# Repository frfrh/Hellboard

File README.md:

# Hellboard

This is a Macro board based on RP2040-zero and Micropython, meant for ordering Stratagems for Helldivers 2 by registering as a HID-Keyboard.

## Hellboard Companion

The Hellboard Companion is a Windows app that puts your stratagems on the Hellboard automatically. It watches the Helldivers 2 loadout screen, recognizes the four stratagems you pick and the optional mission stratagems, and sends them to the board as soon as you press *Ready*. You don't have to configure any buttons by hand. The app also configures the board and installs firmware updates, so you need nothing else to use the Hellboard.

Download it from the [releases](https://github.com/frfrh/Hellboard/releases). More details: [`Software/README.md`](Software/README.md).

### Three stratagems need a one-time setup

The game draws three stratagems differently from the icon set the Companion compares with, so they are reported as *not recognized* at first:

- **EAT-17 Expendable Anti-Tank** and **EAT-411 Leveller** – the game adds a small badge to the icon.
- **TD-220 Bastion MK XVI** – the icon set shows the Maelstrom for it. Until you set it up, a Maelstrom may also be taken for the Bastion.

Teach the Companion how they look in your game – it takes about a minute and is needed only once:

1. Put **all three** into your loadout on the loadout screen (plus any fourth stratagem) and press *Ready* (or close the screen).
2. Open the Companion and go to the **History** tab. You find one entry *Problem: stratagem not recognized* with a picture of the slot for each of them.
3. In each entry, choose the stratagem under **This is …** and click **Use as reference**.

From now on they are recognized and shown with their in-game picture. The pictures stay on your PC; the **Stratagems** tab lists them (*Only with reference*) and can remove them. The same works for any other stratagem that is not recognized, e.g. after a game update changed an icon.

## Folders

##### [Firmware](https://github.com/frfrh/Hellboard/tree/master/Firmware)

Contains the firmware to be loaded into the RP2040 and the Micropython project files.

##### [Hardware](https://github.com/frfrh/Hellboard/tree/master/Hardware)

Contains the 3D files for the case and the button caps.

##### [PCB](https://github.com/frfrh/Hellboard/tree/master/PCB)

Contains the project files for the PCB and the gerber files to order one.
Project is based on KiCad 8.0.2.

##### [Software](https://github.com/frfrh/Hellboard/tree/master/Software)

Contains the Hellboard Companion (C#/.NET, Windows): loadout recognition, transfer to the board, board configuration and firmware updates.

## Configuration

The board is configured in [`Firmware/config.json`](Firmware/config.json); the stratagems and their input codes come from [`doc/stratagems.json`](doc/stratagems.json), the single list used by the firmware and the Companion software (format: [`doc/stratagems.md`](doc/stratagems.md)).

- `fixed`, `loadout`, `multiFunction`: stratagems of the buttons `1_1`/`1_2`, row 2 and the multi-function button `1_3` (cycled with `1_4`), by their `id`.
- `modifierKey`: HID usage id of the stratagem key ([scancodes](https://deskthority.net/wiki/Scancode), e.g. 6 = `C`, 224 = left Ctrl). `modifierToggle: true` presses it once to open the menu, `false` keeps it pressed while the code is entered.
- `directionKeys`: `arrows` or `wasd`; `menuDelayMs`, `keyPressMs`, `keyReleaseMs`: wait for the stratagem menu, how long each arrow is held, pause between arrows (ms); `brightness`: LED brightness (0-255).
- `screenSaverSeconds`: display off after this time without a button press (0 = off); `scrollText`: `off`, `long` (long names scroll back and forth) or `loop` (they run continuously).
- `transferFeedback`: how a received loadout or a save is confirmed – `hellpodHorizontal` (default: a Hellpod animation flying in from the right), `hellpodVertical` (falling from the top) or `flash` (all LEDs flash white). Errors always flash red.

Upload the changed `config.json` to the board (see Setup). With the Hellboard Companion, all of this is set on its *Hellboard* tab instead, and the loadout is taken from the game automatically.

## Build your own

You can use the gerber files in [PCB/gerber](https://github.com/frfrh/Hellboard/tree/master/PCB/gerber) to order your own PCBs or order it directly from https://aisler.net/p/AHPZGPKK.

You will also need the following parts:

| Part | Amount | Link |
| - | - | - |
| RP2040-Zero | 1 | [link](https://www.waveshare.com/rp2040-zero.htm) |
| 0,96" OLED Display 128x64 | 1 | [link](https://de.aliexpress.com/item/1005005970901119.html) (the 26.7mm variant, blue PCB) |
| Kailh boxed switches | 8 | [link](https://www.caseking.de/ducky-kailh-box-navy-switches-mechanisch-3-pin-clicky-mx-stem-85g-110-stueck-gakc-444.html) |
| Kailh hot-swap socket | 8 | [link](https://de.aliexpress.com/item/1005006146911562.html) |
| WS2812b-2020 LED | 8 | [link](https://de.aliexpress.com/item/10000006244752.html) |
| N-Channel MOSFET[^levelshifter] | 1 |  |
| 10K 0805 resistor[^levelshifter] | 2 |  |
| M93C86-WMN6P EEPROM[^eeprom] | 1 | [link](https://www.reichelt.de/eeprom-seriell-16kb-2kx8-1kx16-2-5-5v-so-8-m93c86-wmn6p-p280935.html) |
| Button caps[^buttoncaps] | 8 | [link](https://de.aliexpress.com/item/1005003992982246.html) |

You can find icons for the buttons [here](https://github.com/nvigneux/Helldivers-2-Stratagems-icons-svg).

## Setup

1. Flash MicroPython with HID support onto the RP2040 (only needed once):
    1. Press the button (`Boot`) and connect the Board to a PC.
    2. Copy the [UF2-file](https://github.com/frfrh/Hellboard/blob/master/Firmware/libs/3rd/firmware_with_HID_support.v.1.17.uf2) into the drive `RPI-RP2`.
    3. Re-Connect the board.
2. Install the firmware files. [`Firmware/manifest.json`](Firmware/manifest.json) lists every file and its name on the board (all files go into the board's root directory, including the stratagem list [`doc/stratagems.json`](doc/stratagems.json)).
    - **With the Hellboard Companion** (`Software/`, recommended): connect the board, open the *Hellboard* tab and choose *Update Hellboard firmware*. Later updates work the same way.
    - **With the upload tool** (needs the [.NET 10 SDK](https://dotnet.microsoft.com/download/dotnet/10.0)): from the `Software` folder run `dotnet run tools/hellboard-upload/hellboard-upload.cs`. It finds the board, installs and verifies all files and restarts the board – see [`Software/tools/hellboard-upload`](Software/tools/hellboard-upload/README.md).
    - **By hand** with [Visual Studio Code](https://code.visualstudio.com/) and the [MicroPico extension](https://marketplace.visualstudio.com/items?itemName=paulober.pico-w-go): upload every file listed in the manifest under its target name (`Upload current file to Pico`).
3. Choose your stratagems in [`Firmware/config.json`](Firmware/config.json) (before uploading): buttons `1_1`/`1_2`, the loadout (row 2) and the multi-function list, referenced by their `id` in [`doc/stratagems.json`](doc/stratagems.json); `modifierKey` is the HID usage id of your stratagem key. With the Hellboard Companion (`Software/`), the loadout is set automatically from the game.

[^levelshifter]: I got them by desoldering them from a level shifter I had lying around. [link](https://de.aliexpress.com/item/1005006068381598.html)
[^eeprom]: The EEPROM is optional and currently not used: the configuration is stored in the RP2040's own flash (`config.json`).
[^buttoncaps]: I used the button caps from [here](https://de.aliexpress.com/item/1005003992982246.html) but replaced the internals with the ones from `Hardware/Kailh-Cap.stl` as the original ones are not translucent. Any button caps compatible with Kailh boxed switches should do.

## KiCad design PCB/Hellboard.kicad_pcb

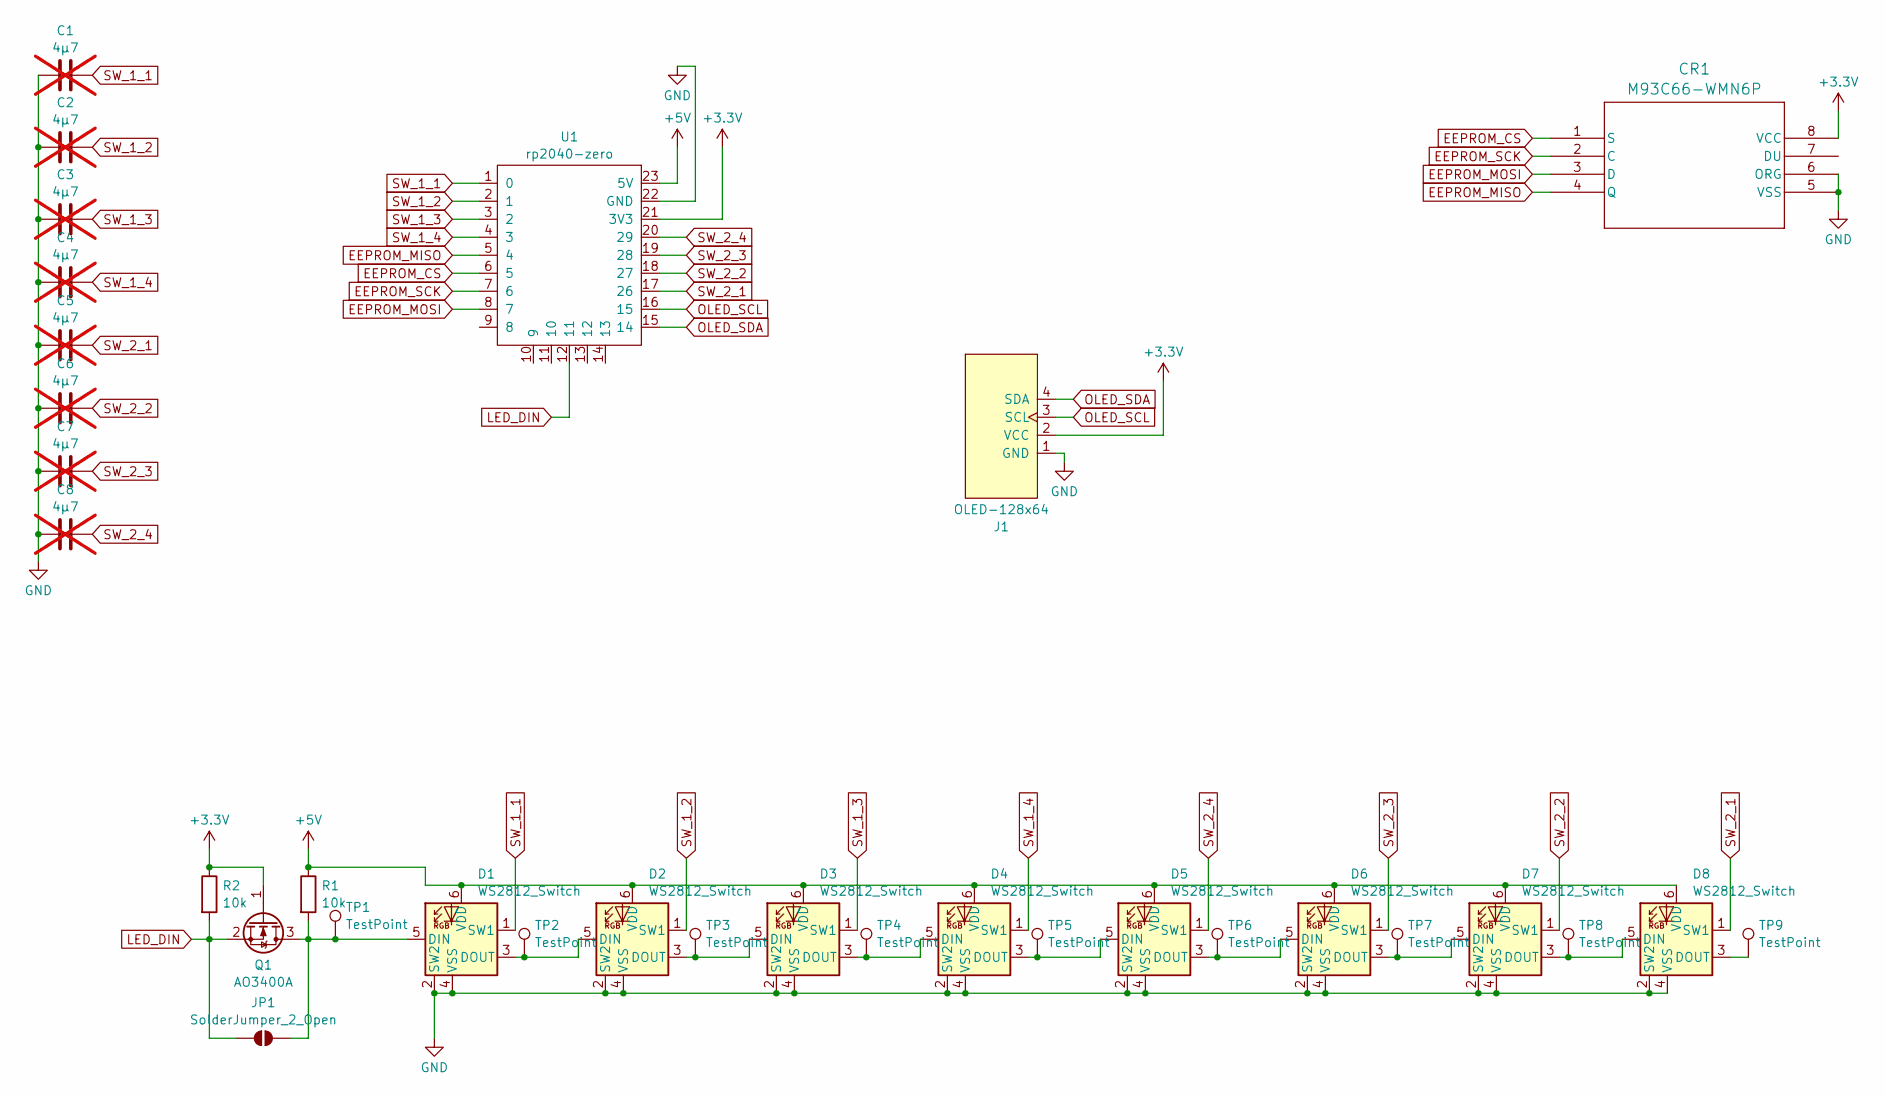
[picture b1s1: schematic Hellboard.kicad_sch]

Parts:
C1, C2, C3, C4, C5, C6, C7, C8: 4µ7; C_0805_2012Metric_Pad1.18x1.45mm_HandSolder; not fitted
CR1: M93C66-WMN6P; SO-8_STM
D1, D2, D3, D4: WS2812_Switch; Kailh_socket_MX_WS2812B_RL
D5, D6, D7, D8: WS2812_Switch; Kailh_socket_MX_WS2812B_LR
J1: OLED-128x64
JP1: SolderJumper_2_Open; SolderJumper-2_P1.3mm_Open_TrianglePad1.0x1.5mm
Q1: AO3400A; SOT-23
R1, R2: 10k; LED_0805_2012Metric_Pad1.15x1.40mm_HandSolder
TP1, TP2, TP3, TP4, TP5, TP6, TP7, TP8, TP9: TestPoint; TestPoint_Pad_D1.5mm
U1: rp2040-zero; rp2040-zero-smd

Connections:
+3.3V: CR1.8 (VCC), J1.2 (VCC), Q1.1 (G), R2.1, U1.21 (3V3)
+5V: D1.6 (VDD), D2.6 (VDD), D3.6 (VDD), D4.6 (VDD), D5.6 (VDD), D6.6 (VDD), D7.6 (VDD), D8.6 (VDD), R1.1, U1.23 (5V)
EEPROM_CS: CR1.1 (S), U1.6 (5)
EEPROM_MISO: CR1.4 (Q), U1.5 (4)
EEPROM_MOSI: CR1.3 (D), U1.8 (7)
EEPROM_SCK: CR1.2 (C), U1.7 (6)
GND: C1.1, C2.1, C3.1, C4.1, C5.1, C6.1, C7.1, C8.1, CR1.5 (VSS), CR1.6 (ORG), D1.2 (SW2), D1.4 (VSS), D2.2 (SW2), D2.4 (VSS), D3.2 (SW2), D3.4 (VSS), D4.2 (SW2), D4.4 (VSS), D5.2 (SW2), D5.4 (VSS), D6.2 (SW2), D6.4 (VSS), D7.2 (SW2), D7.4 (VSS), D8.2 (SW2), D8.4 (VSS), J1.1 (GND), U1.22 (GND)
LED_DIN: JP1.1 (A), Q1.2 (S), R2.2, U1.12 (11)
unnamed: D1.5 (DIN), JP1.2 (B), Q1.3 (D), R1.2, TP1.1
unnamed: D1.3 (DOUT), D2.5 (DIN), TP2.1
unnamed: D2.3 (DOUT), D3.5 (DIN), TP3.1
unnamed: D3.3 (DOUT), D4.5 (DIN), TP4.1
unnamed: D4.3 (DOUT), D5.5 (DIN), TP5.1
unnamed: D5.3 (DOUT), D6.5 (DIN), TP6.1
unnamed: D6.3 (DOUT), D7.5 (DIN), TP7.1
unnamed: D7.3 (DOUT), D8.5 (DIN), TP8.1
unnamed: D8.3 (DOUT), TP9.1
OLED_SCL: J1.3 (SCL), U1.16 (15)
OLED_SDA: J1.4 (SDA), U1.15 (14)
SW_1_1: C1.2, D1.1 (SW1), U1.1 (0)
SW_1_2: C2.2, D2.1 (SW1), U1.2 (1)
SW_1_3: C3.2, D3.1 (SW1), U1.3 (2)
SW_1_4: C4.2, D4.1 (SW1), U1.4 (3)
SW_2_1: C5.2, D8.1 (SW1), U1.17 (26)
SW_2_2: C6.2, D7.1 (SW1), U1.18 (27)
SW_2_3: C7.2, D6.1 (SW1), U1.19 (28)
SW_2_4: C8.2, D5.1 (SW1), U1.20 (29)

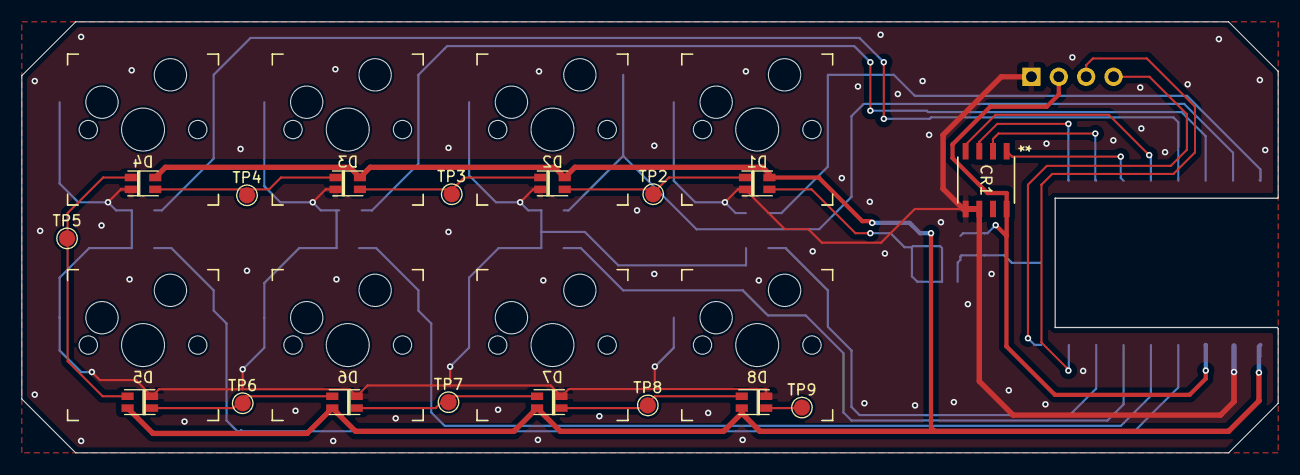
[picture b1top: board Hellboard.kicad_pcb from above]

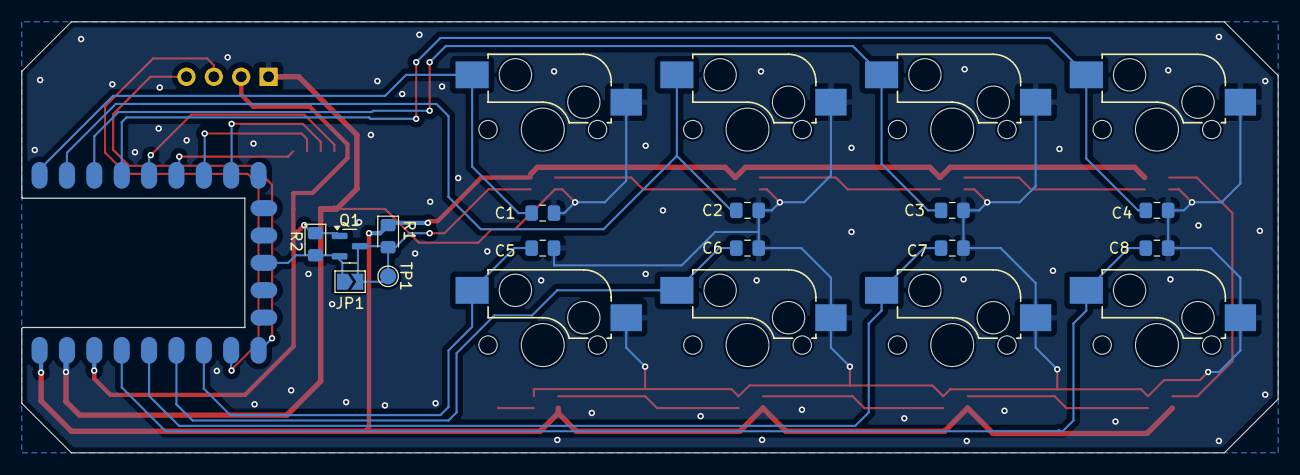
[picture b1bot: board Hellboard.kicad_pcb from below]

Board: 2 copper layers, 116.6 x 40.0 mm, 32 parts (14 on the bottom side), 27 nets.

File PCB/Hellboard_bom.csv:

"Reference","Value","Datasheet","Footprint","Qty","DNP"
"C1,C2,C3,C4,C5,C6,C7,C8","4µ7","~","Capacitor_SMD:C_0805_2012Metric_Pad1.18x1.45mm_HandSolder","8","Nicht bestücken"
"CR1","M93C66-WMN6P","https://www.st.com/resource/en/datasheet/m93c46-w.pdf","footprints_M93C66-WMN6P:SO-8_STM","1",""
"D1,D2,D3,D4,D5,D6,D7,D8","WS2812_Switch","https://cdn-shop.adafruit.com/product-files/4684/4684_WS2812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","-- verschiedene Werte --","8",""
"J1","OLED-128x64","https://www.datasheethub.com/ssd1306-128x64-mono-0-96-inch-i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","display:OLED-128x64","1",""
"Q1","AO3400A","http://www.aosmd.com/pdfs/datasheet/AO3400A.pdf","Package_TO_SOT_SMD:SOT-23","1",""
"R1,R2","10k","~","LED_SMD:LED_0805_2012Metric_Pad1.15x1.40mm_HandSolder","2",""
"TP1,TP2,TP3,TP4,TP5,TP6,TP7,TP8,TP9","TestPoint","~","TestPoint:TestPoint_Pad_D1.5mm","9",""
"U1","rp2040-zero","https://www.waveshare.com/rp2040-zero.htm","mcu:rp2040-zero-smd","1",""

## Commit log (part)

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2024-05-31 gitignore
2024-05-31 adding Hellboard PCB
2024-06-01 add firmware
2024-06-01 add case
2024-06-01 add datasheets
2024-06-01 readme
2024-06-01 license
2024-06-02 Code changes with individual wait timings for better compatibility
2024-06-04 Scrolling text implementation for cycle list elements. Can be enabled/disabled
2024-06-05 fix 120mm barrage
2024-06-16 fix stratagems
2024-06-19 Added Startup-Logo, Scrolling Text on all lines because of burn in effect of oled, and added a "screensaver" of kind that will turn screen to black after timeout.
2024-06-22 Changed from active wait to continuous polling.
2024-06-22 Performace enhancements, I tried at least
2024-07-13 Added 'go back' function for cycle button. Exported button configuration to hellboard_cfg.py Checked macro.py for errors in collor and directions
2024-07-14 Bugfixes
2024-07-27 add MLS-4X Commando
2024-09-04 Orbital Napalm Strike
2026-02-03 Macro updates
2026-02-03 Increase sleep time
